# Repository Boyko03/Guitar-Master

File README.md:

# *Guitar Master*
Have you ever dreamed of learning to play the guitar? Guitar Master will help you make your dream come true!

Read this in other languages: [Bulgarian](https://github.com/Boyko03/Guitar-Master/blob/main/README.bg.md)
## How do I download and use the project?

### Necessary parts
[Parts](https://github.com/Boyko03/Guitar-Master/blob/main/Hardware/parts.csv)

### Download instructions

1) Clone the GitHub repository locally
```bash
  git clone https://github.com/Boyko03/Guitar-Master.git
```
Or download it as a [zip](https://github.com/Boyko03/Guitar-Master/archive/refs/heads/main.zip)

### Installation instructions

1) The Software/main directory contains the program that Arduino Uno runs.
2) Load the program into your Arduino

### Instructions for starting the project

1) It is recommended to solder the elements on the boards included in the repository, but the scheme can also be recreated on a Breadboard.
2) When the elements are connected correctly, a "snake" will appear on the fretboard, and a menu will be displayed on the LCD screen, which is controlled by the buttons.
3) Guitar Master can display notes and chords as well as songs.

## Technologies used

* [KiCad](https://kicad.org/) - A Cross Platform and Open Source Electronics Design Automation Suite
* [Arduino](https://www.arduino.cc/) - Arduino is an open source project for the design and production of an electronic platform with easy-to-use free hardware and software,

## Аbout the authors of the project

* **Boyko Georgiev** - *programmer, designer, hardware engineer* - [Boyko03](https://github.com/Boyko03)

## Photos and demonstration
[Electric Schema](https://github.com/Boyko03/Guitar-Master/blob/main/Hardware/guitar.pdf) <br />
[Demo](https://github.com/Boyko03/Guitar-Master/blob/main/Presentation/demo.mp4) <br />

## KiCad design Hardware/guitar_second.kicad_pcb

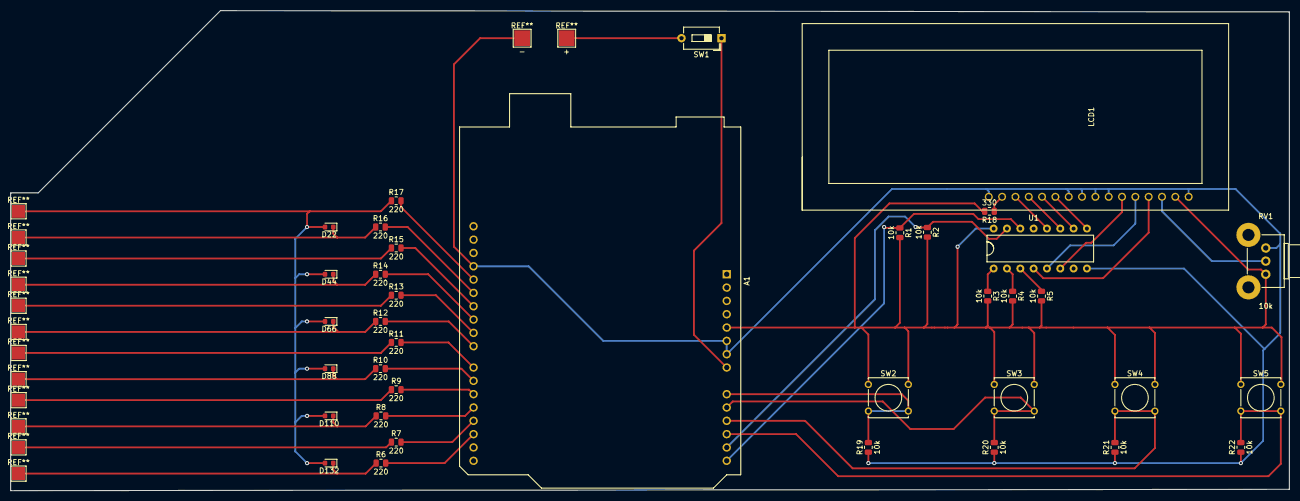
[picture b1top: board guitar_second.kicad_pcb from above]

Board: 2 copper layers, 243.8 x 91.5 mm, 37 parts (0 on the bottom side), 40 nets.

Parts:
A1: Arduino_UNO_R3
D22: 12-11; LED_0603_1608Metric
D44: 12-9; LED_0603_1608Metric
D66: 12-7; LED_0603_1608Metric
D88: 12-5; LED_0603_1608Metric
D110: 12-3; LED_0603_1608Metric
D132: 12-1; LED_0603_1608Metric
LCD1: 1602A
R1, R2, R3, R4, R5, R19, R20, R21, R22: 10k; R_0805_2012Metric
R6, R7, R8, R9, R10, R11, R12, R13, R14, R15, R16, R17: 220; R_0805_2012Metric
R18: 330; R_0805_2012Metric
RV1: 10k; Potentiometer_Alps_RK09K_Single_Horizontal
SW1: SW_Push; SW_DIP_SPSTx01_Slide_6.7x4.1mm_W7.62mm_P2.54mm_LowProfile
SW2, SW3, SW4, SW5: SW_Push; SW_Tactile_Straight_KSA0Axx1LFTR
U1: PCF8574

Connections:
+5V: A1.5, LCD1.2, R1.2, R2.2, R3.2, R4.2, R5.2, R18.2, RV1.1, SW2.1, SW3.1, SW4.1, SW5.1, U1.16
/A0: A1.9, R19.2, SW2.2
/A1: A1.10, R20.2, SW3.2
/A2: A1.11, R21.2, SW4.2
/A3: A1.12, R22.2, SW5.2
/LCD_D4: LCD1.11, U1.9
/LCD_D5: LCD1.12, U1.10
/LCD_D6: LCD1.13, U1.11
/LCD_D7: LCD1.14, U1.12
/LCD_E: LCD1.6, U1.6
/LCD_RS: LCD1.4, U1.4
/LCD_RW: LCD1.5, U1.5
/P1: D132.1, R6.1
/P3: D110.1, R8.1
/P5: D88.1, R10.1
/P7: D66.1, R12.1
/P9: D44.1, R14.1
/P11: D22.1, R16.1
/P12: D22.2, D44.2, D66.2, D88.2, D110.2, D132.2, R17.1
/SCL: A1.14, R1.1, U1.14
/SDA: A1.13, R2.1, U1.15
GND: A1.6, A1.7, A1.29, LCD1.1, LCD1.7, LCD1.8, LCD1.9, LCD1.10, LCD1.16, R19.1, R20.1, R21.1, R22.1, RV1.3, U1.8
unnamed: A1.8, SW1.1
unnamed: A1.17, R6.2
unnamed: A1.18, R7.2
unnamed: A1.19, R8.2
unnamed: A1.20, R9.2
unnamed: A1.21, R10.2
unnamed: A1.22, R11.2
unnamed: A1.23, R12.2
unnamed: A1.24, R13.2
unnamed: A1.25, R14.2
unnamed: A1.26, R15.2
unnamed: A1.27, R16.2
unnamed: A1.28, R17.2
unnamed: LCD1.3, RV1.2
unnamed: LCD1.15, R18.1
unnamed: R3.1, U1.1
unnamed: R4.1, U1.2
unnamed: R5.1, U1.3

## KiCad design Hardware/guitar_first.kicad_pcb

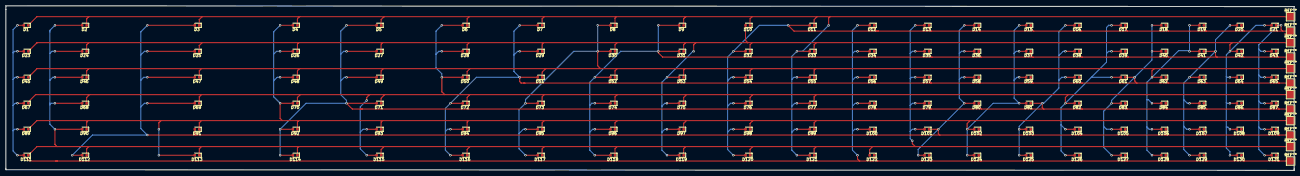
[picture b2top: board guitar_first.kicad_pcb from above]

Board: 2 copper layers, 446.2 x 57.0 mm, 126 parts (0 on the bottom side), 12 nets.

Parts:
D1: 1-12; LED_0603_1608Metric
D2: 2-12; LED_0603_1608Metric
D3: 3-12; LED_0603_1608Metric
D4: 4-12; LED_0603_1608Metric
D5: 5-12; LED_0603_1608Metric
D6: 6-12; LED_0603_1608Metric
D7: 7-12; LED_0603_1608Metric
D8: 8-12; LED_0603_1608Metric
D9: 9-12; LED_0603_1608Metric
D10: 10-12; LED_0603_1608Metric
D11: 11-12; LED_0603_1608Metric
D12: 1-11; LED_0603_1608Metric
D13: 2-11; LED_0603_1608Metric
D14: 3-11; LED_0603_1608Metric
D15: 4-11; LED_0603_1608Metric
D16: 5-11; LED_0603_1608Metric
D17: 6-11; LED_0603_1608Metric
D18: 7-11; LED_0603_1608Metric
D19: 8-11; LED_0603_1608Metric
D20: 9-11; LED_0603_1608Metric
D21: 10-11; LED_0603_1608Metric
D23: 1-10; LED_0603_1608Metric
D24: 2-10; LED_0603_1608Metric
D25: 3-10; LED_0603_1608Metric
D26: 4-10; LED_0603_1608Metric
D27: 5-10; LED_0603_1608Metric
D28: 6-10; LED_0603_1608Metric
D29: 7-10; LED_0603_1608Metric
D30: 8-10; LED_0603_1608Metric
D31: 9-10; LED_0603_1608Metric
D32: 11-10; LED_0603_1608Metric
D33: 12-10; LED_0603_1608Metric
D34: 1-9; LED_0603_1608Metric
D35: 2-9; LED_0603_1608Metric
D36: 3-9; LED_0603_1608Metric
D37: 4-9; LED_0603_1608Metric
D38: 5-9; LED_0603_1608Metric
D39: 6-9; LED_0603_1608Metric
D40: 7-9; LED_0603_1608Metric
D41: 8-9; LED_0603_1608Metric
D42: 10-9; LED_0603_1608Metric
D43: 11-9; LED_0603_1608Metric
D45: 1-8; LED_0603_1608Metric
D46: 2-8; LED_0603_1608Metric
D47: 3-8; LED_0603_1608Metric
D48: 4-8; LED_0603_1608Metric
D49: 5-8; LED_0603_1608Metric
D50: 6-8; LED_0603_1608Metric
D51: 7-8; LED_0603_1608Metric
D52: 9-8; LED_0603_1608Metric
D53: 10-8; LED_0603_1608Metric
D54: 11-8; LED_0603_1608Metric
D55: 12-8; LED_0603_1608Metric
D56: 1-7; LED_0603_1608Metric
D57: 2-7; LED_0603_1608Metric
D58: 3-7; LED_0603_1608Metric
D59: 4-7; LED_0603_1608Metric
D60: 5-7; LED_0603_1608Metric
D61: 6-7; LED_0603_1608Metric
D62: 8-7; LED_0603_1608Metric
D63: 9-7; LED_0603_1608Metric
D64: 10-7; LED_0603_1608Metric
D65: 11-7; LED_0603_1608Metric
D67: 1-6; LED_0603_1608Metric
D68: 2-6; LED_0603_1608Metric
D69: 3-6; LED_0603_1608Metric
D70: 4-6; LED_0603_1608Metric
D71: 5-6; LED_0603_1608Metric
D72: 7-6; LED_0603_1608Metric
D73: 8-6; LED_0603_1608Metric
D74: 9-6; LED_0603_1608Metric
D75: 10-6; LED_0603_1608Metric
D76: 11-6; LED_0603_1608Metric
D77: 12-6; LED_0603_1608Metric
D78: 1-5; LED_0603_1608Metric
D79: 2-5; LED_0603_1608Metric
D80: 3-5; LED_0603_1608Metric
D81: 4-5; LED_0603_1608Metric
D82: 6-5; LED_0603_1608Metric
D83: 7-5; LED_0603_1608Metric
D84: 8-5; LED_0603_1608Metric
D85: 9-5; LED_0603_1608Metric
D86: 10-5; LED_0603_1608Metric
D87: 11-5; LED_0603_1608Metric
D89: 1-4; LED_0603_1608Metric
D90: 2-4; LED_0603_1608Metric
D91: 3-4; LED_0603_1608Metric
D92: 5-4; LED_0603_1608Metric
D93: 6-4; LED_0603_1608Metric
D94: 7-4; LED_0603_1608Metric
D95: 8-4; LED_0603_1608Metric
D96: 9-4; LED_0603_1608Metric
D97: 10-4; LED_0603_1608Metric
D98: 11-4; LED_0603_1608Metric
D99: 12-4; LED_0603_1608Metric
D100: 1-3; LED_0603_1608Metric
D101: 2-3; LED_0603_1608Metric
D102: 4-3; LED_0603_1608Metric
D103: 5-3; LED_0603_1608Metric
D104: 6-3; LED_0603_1608Metric
D105: 7-3; LED_0603_1608Metric
D106: 8-3; LED_0603_1608Metric
D107: 9-3; LED_0603_1608Metric
D108: 10-3; LED_0603_1608Metric
D109: 11-3; LED_0603_1608Metric
D111: 1-2; LED_0603_1608Metric
D112: 3-2; LED_0603_1608Metric
D113: 4-2; LED_0603_1608Metric
D114: 5-2; LED_0603_1608Metric
D115: 6-2; LED_0603_1608Metric
D116: 7-2; LED_0603_1608Metric
D117: 8-2; LED_0603_1608Metric
D118: 9-2; LED_0603_1608Metric
D119: 10-2; LED_0603_1608Metric
D120: 11-2; LED_0603_1608Metric
D121: 12-2; LED_0603_1608Metric
D122: 2-1; LED_0603_1608Metric
D123: 3-1; LED_0603_1608Metric
D124: 4-1; LED_0603_1608Metric
D125: 5-1; LED_0603_1608Metric
D126: 6-1; LED_0603_1608Metric
D127: 7-1; LED_0603_1608Metric
D128: 8-1; LED_0603_1608Metric
D129: 9-1; LED_0603_1608Metric
D130: 10-1; LED_0603_1608Metric
D131: 11-1; LED_0603_1608Metric

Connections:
/P1: D1.2, D12.2, D23.2, D34.2, D45.2, D56.2, D67.2, D78.2, D89.2, D100.2, D111.2, D122.1, D123.1, D124.1, D125.1, D126.1, D127.1, D128.1, D129.1, D130.1, D131.1
/P2: D2.2, D13.2, D24.2, D35.2, D46.2, D57.2, D68.2, D79.2, D90.2, D101.2, D111.1, D112.1, D113.1, D114.1, D115.1, D116.1, D117.1, D118.1, D119.1, D120.1, D121.1, D122.2
/P3: D3.2, D14.2, D25.2, D36.2, D47.2, D58.2, D69.2, D80.2, D91.2, D100.1, D101.1, D102.1, D103.1, D104.1, D105.1, D106.1, D107.1, D108.1, D109.1, D112.2, D123.2
/P4: D4.2, D15.2, D26.2, D37.2, D48.2, D59.2, D70.2, D81.2, D89.1, D90.1, D91.1, D92.1, D93.1, D94.1, D95.1, D96.1, D97.1, D98.1, D99.1, D102.2, D113.2, D124.2
/P5: D5.2, D16.2, D27.2, D38.2, D49.2, D60.2, D71.2, D78.1, D79.1, D80.1, D81.1, D82.1, D83.1, D84.1, D85.1, D86.1, D87.1, D92.2, D103.2, D114.2, D125.2
/P6: D6.2, D17.2, D28.2, D39.2, D50.2, D61.2, D67.1, D68.1, D69.1, D70.1, D71.1, D72.1, D73.1, D74.1, D75.1, D76.1, D77.1, D82.2, D93.2, D104.2, D115.2, D126.2
/P7: D7.2, D18.2, D29.2, D40.2, D51.2, D56.1, D57.1, D58.1, D59.1, D60.1, D61.1, D62.1, D63.1, D64.1, D65.1, D72.2, D83.2, D94.2, D105.2, D116.2, D127.2
/P8: D8.2, D19.2, D30.2, D41.2, D45.1, D46.1, D47.1, D48.1, D49.1, D50.1, D51.1, D52.1, D53.1, D54.1, D55.1, D62.2, D73.2, D84.2, D95.2, D106.2, D117.2, D128.2
/P9: D9.2, D20.2, D31.2, D34.1, D35.1, D36.1, D37.1, D38.1, D39.1, D40.1, D41.1, D42.1, D43.1, D52.2, D63.2, D74.2, D85.2, D96.2, D107.2, D118.2, D129.2
/P10: D10.2, D21.2, D23.1, D24.1, D25.1, D26.1, D27.1, D28.1, D29.1, D30.1, D31.1, D32.1, D33.1, D42.2, D53.2, D64.2, D75.2, D86.2, D97.2, D108.2, D119.2, D130.2
/P11: D11.2, D12.1, D13.1, D14.1, D15.1, D16.1, D17.1, D18.1, D19.1, D20.1, D21.1, D32.2, D43.2, D54.2, D65.2, D76.2, D87.2, D98.2, D109.2, D120.2, D131.2
/P12: D1.1, D2.1, D3.1, D4.1, D5.1, D6.1, D7.1, D8.1, D9.1, D10.1, D11.1, D33.2, D55.2, D77.2, D99.2, D121.2

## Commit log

2021-03-23 Added guitar project files (pcb, electric schema etc)
2021-03-23 Added Gerber and Drill files
2021-03-23 Added code for menu
2021-03-23 Updated README. TODO update README
2021-04-10 Added electric schema as pdf
2021-04-18 Added notes and chords + demo
2021-04-18 Added photos of project and a demo video
2021-04-21 Fixed pin numbering of port expander
2021-12-08 Update README (English)
